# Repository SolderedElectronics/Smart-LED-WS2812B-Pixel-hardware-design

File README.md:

# Smart LED WS2812B Pixel Hardware Design

## About the Product

|  |
| :----------------------------------------------------------: |
| [Buy Smart LED WS2812B Pixel](https://www.solde.red/333054) |

These small LEDs are not just ordinary lights – each is unique because it has a built-in small integrated circuit (IC) that is able to turn on the LED light in 16 million different colors. IC is WS2812 and it uses a single wire that can control thousands of these LEDs. With a little imagination by putting these pixels, you get superior effects with a minimum effort. These lamps are easy to control with Dasduino.

---

## Repository Contents

This repository contains all design files for Smart LED WS2812B Pixel, organized as follows:

- **`CAD` folder**: Contains KiCAD design files, including:
  - Schematics
  - PCB layout
  - Panel PCB layout
  - Source 3D files in Fusion360, if any
  - All files are sorted by version with a detailed change log.
- **`OUTPUTS` folder**: Includes all production-ready files, such as:
  - Bill of Materials (BOM) and interactive BOM (iBOM)
  - PDF versions of schematics
  - 3D `.step` file of the board
  - 3D-printable models
  - Gerber files for PCB manufacturing
  - Image of the pinout of the board
  - Product image
  - Compliance, legal and generic sales documents

Refer to the `Change Log` in the CAD folder for details about updates between versions.

---

## Learn More About the Product

Beyond the repository, explore the following resources:

### Soldered Verify

The **Soldered Verify** system ensures every board you purchase from Soldered is fully functional. It also provides access to exclusive test data for your product. To get started, find the unique Soldered Verify ID on your product's packaging and enter the ID on the [Soldered Verify page](https://soldered.com/verify/) to access test results and additional product details.

### Soldered Community

Soldered Community is your go-to place for technical support. Our engineers track and answer all questions posted there, and it’s a great space for the maker community. Get answers to your questions and solutions for your challenges at [Soldered Community](https://soldered.com/community).

### solde.red

solde.red is an ultimate URL shortener and information hub. Access it by typing solde.red/ followed by your product SKU, e.g., [solde.red/333000](https://solde.red/333000), to find getting-started guides, datasheets, open-source hardware and software files, certifications, images, pinouts, and more. Read more about the shortener [here](https://solde.red/info/).

---

## Contributing

Contributions are welcome! Here’s how you can get involved:

- Submit pull requests to enhance the design or fix issues.
- Report bugs or problems by opening an issue.

We encourage community collaboration to make this product even better.

---

## About Soldered

[Soldered for Makers](https://soldered.com) specializes in designing and manufacturing electronic products tailored for enthusiasts, ranging from hobbyists to professionals. Our portfolio includes electronic boards, sensors, and actuators that are widely utilized in fields such as microelectronics, mechatronics, robotics, programming, and IoT. Every product we offer is designed in-house and built upon open-source hardware and software platforms. Proudly certified and manufactured within the European Union, our catalog likely includes the product you need for your project.

We complement these products with comprehensive tutorials and manuals, product descriptions, schematics, programming codes, and project examples. Our round-the-clock [customer and technical support](https://soldered.com/community) is available for all our products, irrespective of the sales channel. Soldered’s success and services reflect our maker community’s unwavering [trust](https://www.trustpilot.com/review/soldered.com), for which we are deeply grateful. Join our community and create using Soldered products.

---

## License

All Soldered open-source hardware (OSH) is under The TAPR Open Hardware License. Read more in the LICENSE file located in this repository.

**Disclaimer:**

No warranty - all designs in this repository are distributed in the hope that they will be useful, but without any warranty. They are provided "AS IS", therefore without warranty of any kind, either expressed or implied. The entire quality and performance of what you do with the contents of this repository are your responsibility. In no event Soldered Electronics will be liable for your damages, or losses, including any general, special, incidental, or consequential damage arising out of the use or inability to use the contents of this repository. 

---

## Have fun!

Thank you for your support from your fellow makers at Soldered Electronics.

Happy Making!

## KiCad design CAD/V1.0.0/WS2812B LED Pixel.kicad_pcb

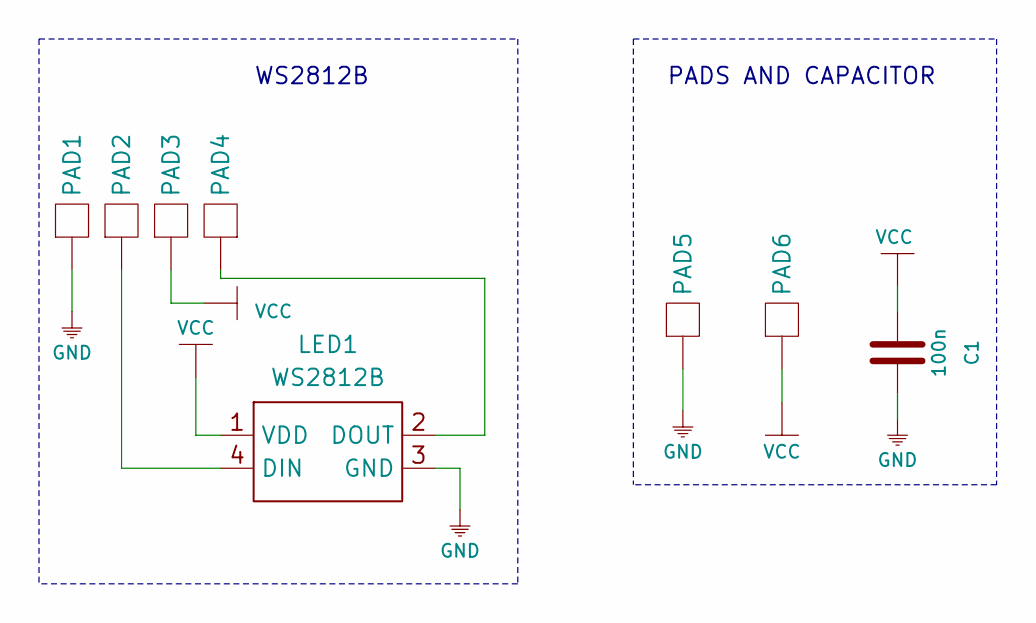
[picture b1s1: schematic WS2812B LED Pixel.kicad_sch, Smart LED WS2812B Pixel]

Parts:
C1: 100n; 0603C
LED1: WS2812B; WS2812B LED
PAD1, PAD2, PAD3, PAD4, PAD5, PAD6: PAD_2x1.5

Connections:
GND: C1.2, LED1.3 (GND), PAD1.1, PAD5.1
unnamed: LED1.2 (DOUT), PAD4.1
unnamed: LED1.4 (DIN), PAD2.1
VCC: C1.1, LED1.1 (VDD), PAD3.1, PAD6.1

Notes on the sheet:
WS2812B
PADS AND CAPACITOR

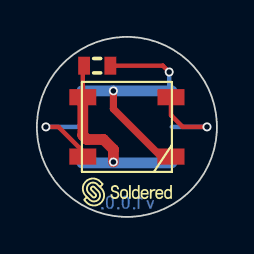
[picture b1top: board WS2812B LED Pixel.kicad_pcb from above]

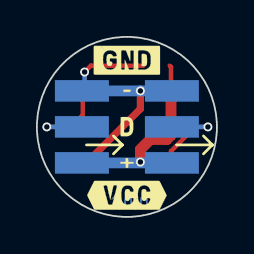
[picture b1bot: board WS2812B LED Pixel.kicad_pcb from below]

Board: 2 copper layers, 10.0 x 10.0 mm, 9 parts (7 on the bottom side), 4 nets.

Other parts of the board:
Ref**: Val**; Version1.0.0.

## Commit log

2022-08-06 Updating open source files.
